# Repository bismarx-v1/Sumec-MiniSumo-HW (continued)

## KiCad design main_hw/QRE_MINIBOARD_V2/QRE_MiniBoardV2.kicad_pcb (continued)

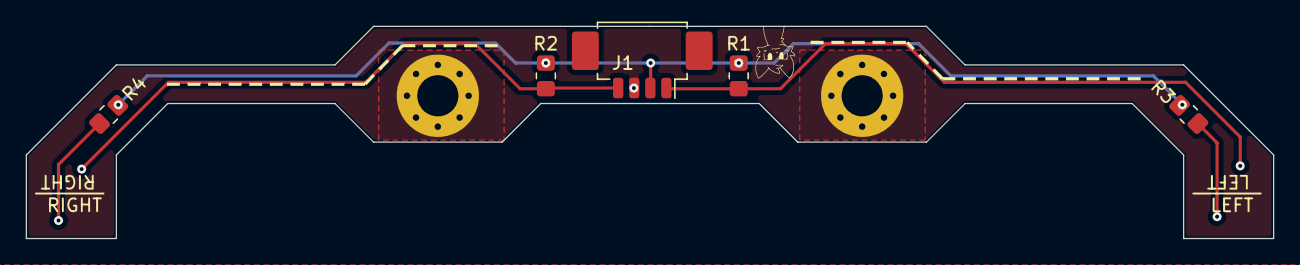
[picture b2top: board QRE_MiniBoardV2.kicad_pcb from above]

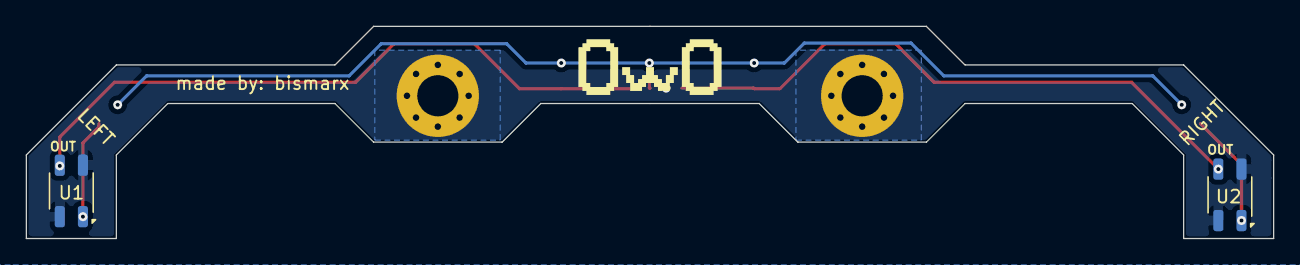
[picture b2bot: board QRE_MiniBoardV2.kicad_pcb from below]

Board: 2 copper layers, 97.0 x 16.5 mm, 11 parts (3 on the bottom side), 6 nets.

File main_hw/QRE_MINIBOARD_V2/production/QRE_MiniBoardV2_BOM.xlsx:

Designator | Footprint | Quantity | Value | Link
J1 | Molex_PicoBlade_53261-0471_1x04-1MP_P1.25mm_Horizontal | 1 | Conn_01x04_Pin | Molex PicoBlade, 4 Pin, horizontal, mouser
R1, R2 | 0805 | 2 | 10k
R3, R4 | 0805 | 2 | 100R
U1, U2 | OnSemi_CASE100CY | 2 | QRE1113 | QRE1113GR

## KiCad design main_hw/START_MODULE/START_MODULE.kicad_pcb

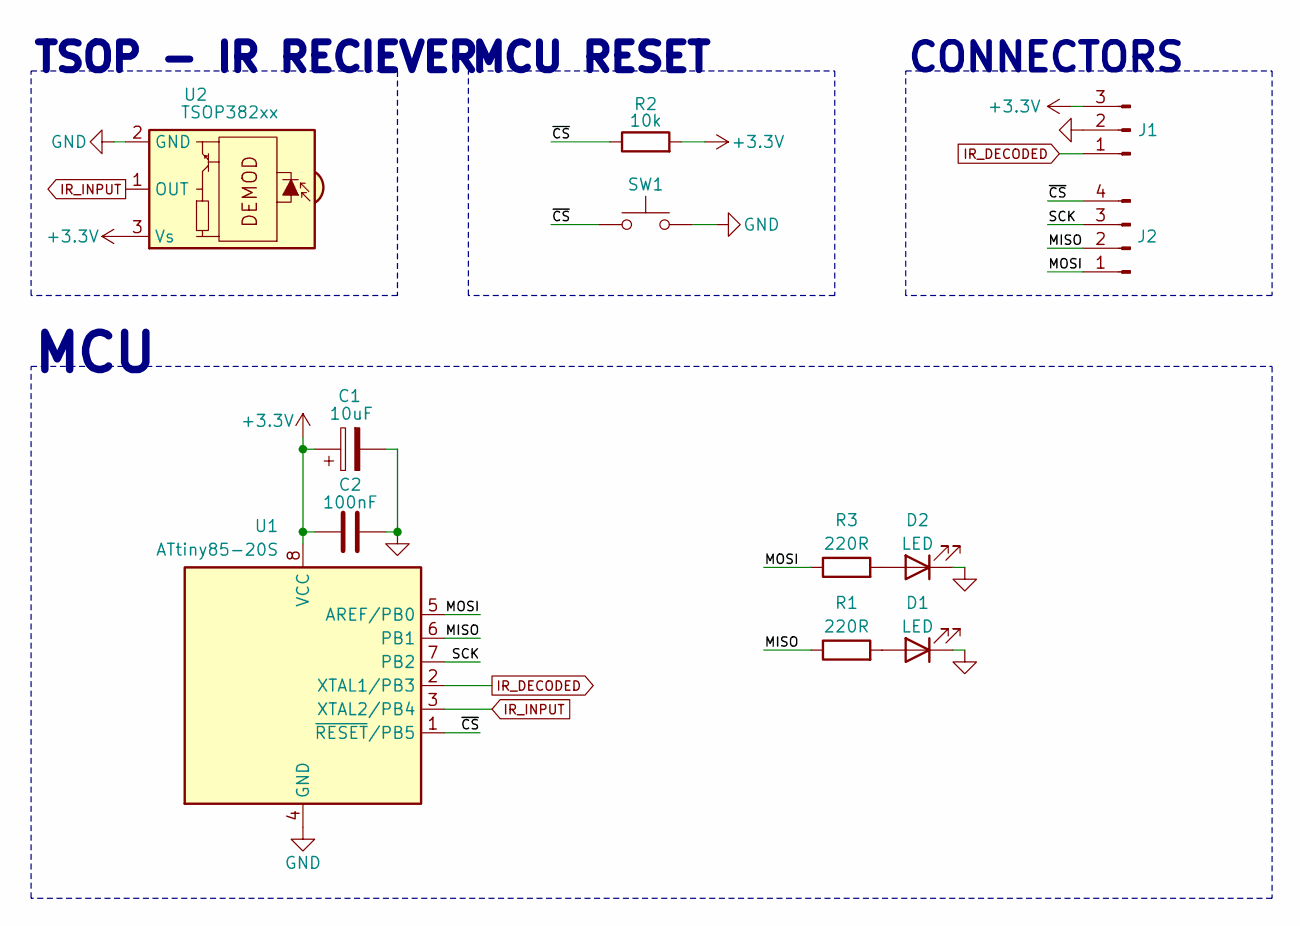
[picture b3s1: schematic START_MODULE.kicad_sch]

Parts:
C1: 10uF; CP_EIA-3216-18_Kemet-A_Pad1.58x1.35mm_HandSolder
C2: 100nF; C_0805_2012Metric_Pad1.18x1.45mm_HandSolder
D1, D2: LED; LED_0805_2012Metric_Pad1.15x1.40mm_HandSolder
J1: Conn_01x03_Pin; PinHeader_1x03_P2.54mm_Horizontal
J2: Conn_01x04_Pin; PinHeader_1x04_P2.54mm_Vertical
R1, R3: 220R; R_0805_2012Metric_Pad1.20x1.40mm_HandSolder
R2: 10k; R_0805_2012Metric_Pad1.20x1.40mm_HandSolder
SW1: SW_Push; SW_SPST_EVQPE1
U1: ATtiny85-20S; SOIC-8W_5.3x5.3mm_P1.27mm
U2: TSOP382xx; Vishay_MINICAST-3Pin

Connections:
+3.3V: C1.1, C2.1, J1.3, R2.2, U1.8 (VCC), U2.3 (Vs)
/MISO: J2.2, R1.1, U1.6 (PB1)
/MOSI: J2.1, R3.1, U1.5 (AREF/PB0)
/SCK: J2.3, U1.7 (PB2)
/~CS: J2.4, R2.1, SW1.2, U1.1 (~RESET/PB5)
GND: C1.2, C2.2, D1.1 (K), D2.1 (K), J1.2, SW1.1, U1.4 (GND), U2.2 (GND)
IR_DECODED: J1.1, U1.2 (XTAL1/PB3)
IR_INPUT: U1.3 (XTAL2/PB4), U2.1 (OUT)
unnamed: D1.2 (A), R1.2
unnamed: D2.2 (A), R3.2

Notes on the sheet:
MCU
TSOP - IR RECIEVER
CONNECTORS
MCU RESET

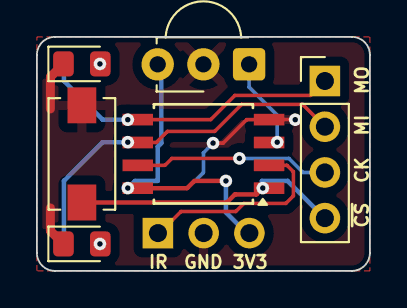
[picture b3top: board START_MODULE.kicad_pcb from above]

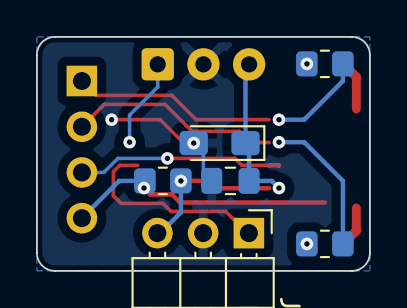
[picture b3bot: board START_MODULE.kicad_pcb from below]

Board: 2 copper layers, 18.5 x 13.0 mm, 12 parts (6 on the bottom side), 10 nets.

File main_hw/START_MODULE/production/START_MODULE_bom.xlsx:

Designator | Footprint | Quantity | Value | Link
C1 | CP_EIA-3216-18_Kemet-A_Pad1.58x1.35mm_HandSolder | 1 | 10uF
C2 | 0805 | 1 | 100nF
D1, D2 | 0805 | 2 | LED
R1, R3 | 0805 | 2 | 220R
R2 | 0805 | 1 | 10k
J1 | PinHeader_1x03_P2.54mm_Vertical | 1 | Conn_01x03_Pin
J2 | PinHeader_1x04_P2.54mm_Vertical | 1 | Conn_01x04_Pin
SW1 | SW_SPST_EVQPE1 | 1 | SW_Push
U1 | SOIC-8W_5.3x5.3mm_P1.27mm | 1 | ATtiny85-20S | ATtiny85-20S
U2 | Vishay_MINICAST-3Pin | 1 | TSOP382xx

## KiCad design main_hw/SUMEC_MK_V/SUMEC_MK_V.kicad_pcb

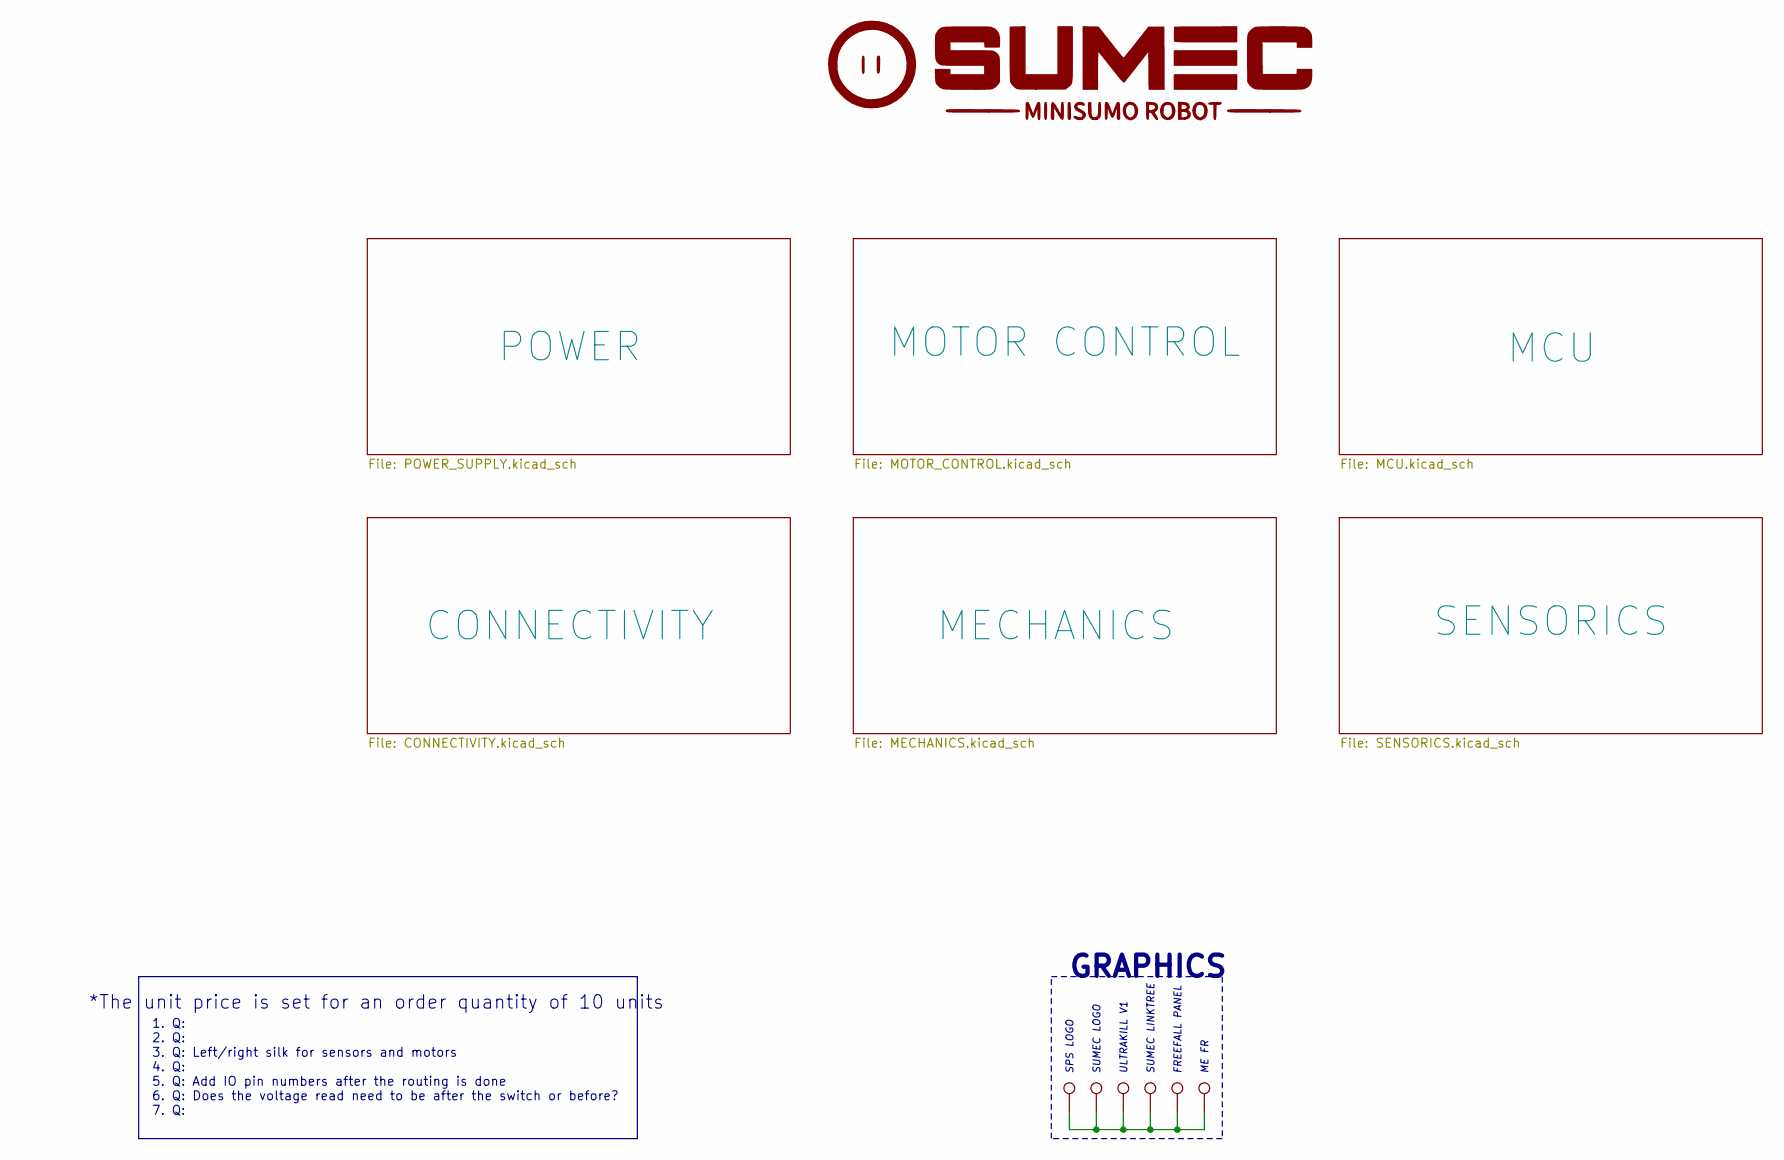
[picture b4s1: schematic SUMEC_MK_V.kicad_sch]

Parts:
TP1, TP2, TP3, TP4, TP5, TP6: TestPoint

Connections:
unnamed: TP1.1, TP2.1, TP3.1, TP4.1, TP5.1, TP6.1

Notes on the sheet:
SUMEC LINKTREE
GRAPHICS
ULTRAKILL V1
1. Q: 2. Q: 3. Q: Left/right silk for sensors and motors 4. Q: 5. Q: Add IO pin numbers after the routing is done 6. Q: Does the voltage read need to be after the switch or before? 7. Q:
SPS LOGO
*The unit price is set for an order quantity of 10 units
SUMEC LOGO
ME FR
FREEFALL PANEL

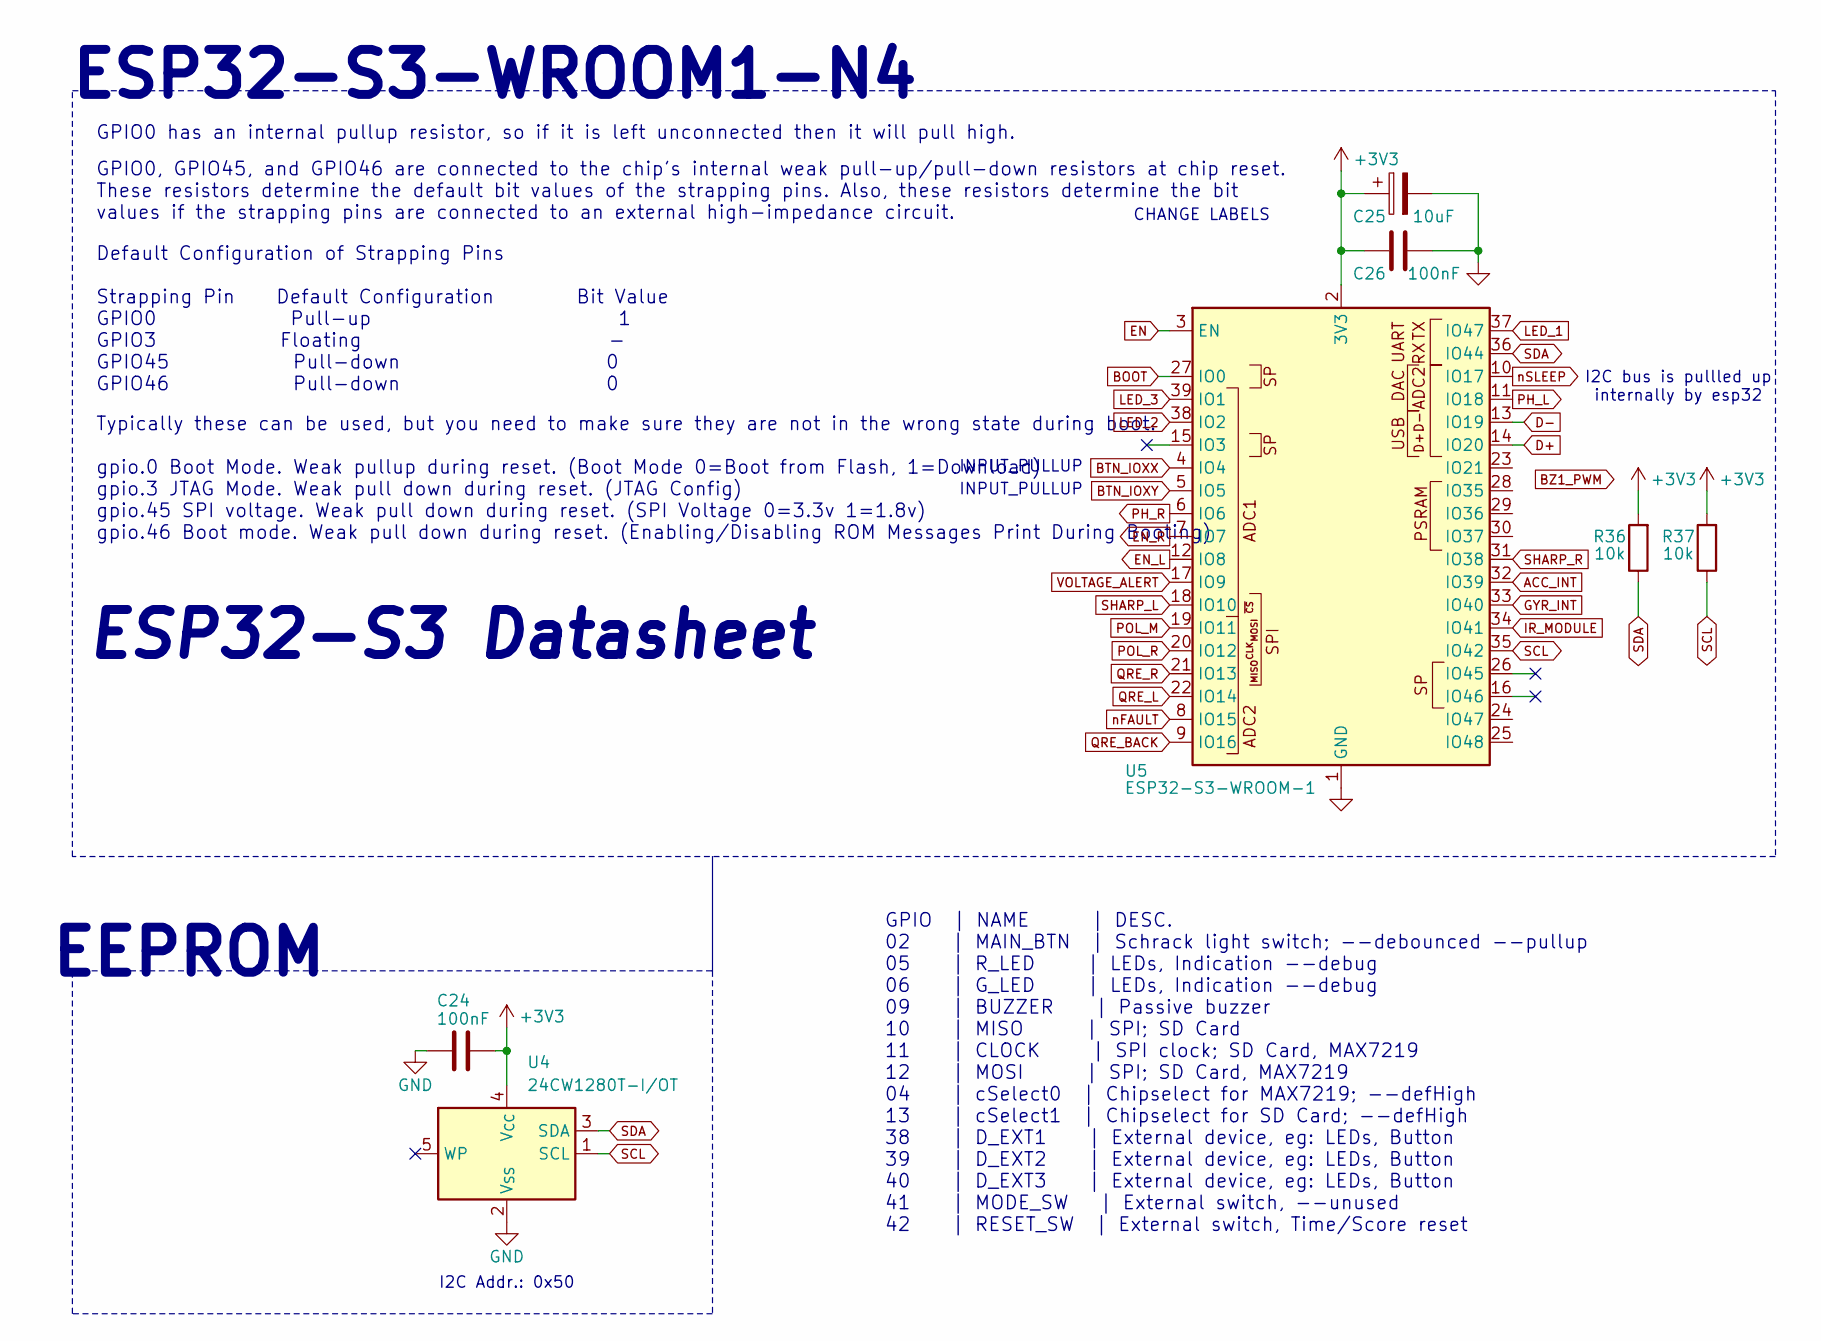
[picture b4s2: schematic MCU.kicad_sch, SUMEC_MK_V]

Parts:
C24, C26: 100nF; C_0805_2012Metric_Pad1.18x1.45mm_HandSolder
C25: 10uF; CP_EIA-3216-18_Kemet-A_Pad1.58x1.35mm_HandSolder
R36, R37: 10k; R_0805_2012Metric_Pad1.20x1.40mm_HandSolder
U4: 24CW1280T-I/OT; SOT-23-5
U5: ESP32-S3-WROOM-1

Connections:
+3V3: C24.1, C25.1, C26.1, R36.2, R37.2, U4.4 (V_{CC}), U5.2 (3V3); also elsewhere on the board
ACC_INT: U5.32 (IO39); also elsewhere on the board
BOOT: U5.27 (IO0); also elsewhere on the board
BTN_IOXX: U5.4 (IO4); also elsewhere on the board
BTN_IOXY: U5.5 (IO5); also elsewhere on the board
D+: U5.14 (IO20); also elsewhere on the board
D-: U5.13 (IO19); also elsewhere on the board
EN: U5.3 (EN); also elsewhere on the board
EN_L: U5.12 (IO8); also elsewhere on the board
EN_R: U5.7 (IO7); also elsewhere on the board
GND: C24.2, C25.2, C26.2, U4.2 (V_{SS}), U5.1 (GND), U5.40 (GND), U5.41 (GND); also elsewhere on the board
GYR_INT: U5.33 (IO40); also elsewhere on the board
IR_MODULE: U5.34 (IO41); also elsewhere on the board
LED_1: U5.37 (IO47); also elsewhere on the board
LED_2: U5.38 (IO2); also elsewhere on the board
LED_3: U5.39 (IO1); also elsewhere on the board
PH_L: U5.11 (IO18); also elsewhere on the board
PH_R: U5.6 (IO6); also elsewhere on the board
POL_M: U5.19 (IO11); also elsewhere on the board
POL_R: U5.20 (IO12); also elsewhere on the board
QRE_BACK: U5.9 (IO16); also elsewhere on the board
QRE_L: U5.22 (IO14); also elsewhere on the board
QRE_R: U5.21 (IO13); also elsewhere on the board
SCL: R37.1, U4.1 (SCL), U5.35 (IO42); also elsewhere on the board
SDA: R36.1, U4.3 (SDA), U5.36 (IO44); also elsewhere on the board
SHARP_L: U5.18 (IO10); also elsewhere on the board
SHARP_R: U5.31 (IO38); also elsewhere on the board
VOLTAGE_ALERT: U5.17 (IO9); also elsewhere on the board
nFAULT: U5.8 (IO15); also elsewhere on the board
nSLEEP: U5.10 (IO17); also elsewhere on the board

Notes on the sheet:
Typically these can be used, but you need to make sure they are not in the wrong state during boot. gpio.0 Boot Mode. Weak pullup during reset. (Boot Mode 0=Boot from Flash, 1=Download) gpio.3 JTAG Mode. Weak pull down during reset. (JTAG Config) gpio.45 SPI voltage. Weak pull down during reset. (S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
GPIO0 has an internal pullup resistor, so if it is left unconnected then it will pull high.
GPIO | NAME | DESC. 02 | MAIN_BTN | Schrack light switch; --debounced --pullup 05 | R_LED | LEDs, Indication --debug 06 | G_LED | LEDs, Indication --debug 09 | BUZZER | Passive buzzer 10 | MISO | SPI; SD Card 11 | CLOCK | SPI clock; SD Card, MAX7219 12 | MOSI | SPI; SD Card, MAX7219 04 | cSelect0 |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
ESP32-S3-WROOM1-N4
I2C Addr.: 0x50
GPIO0, GPIO45, and GPIO46 are connected to the chip's internal weak pull-up/pull-down resistors at chip reset. These resistors determine the default bit values of the strapping pins. Also, these resistors determine the bit values if the strapping pins are connected to an external high-impedance cir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
CHANGE LABELS
I2C bus is pullled up internally by esp32
ESP32-S3 Datasheet
INPUT_PULLUP
EEPROM
Default Configuration of Strapping Pins Strapping Pin Default Configuration Bit Value GPIO0 Pull-up 1 GPIO3 Floating - GPIO45 Pull-down 0 GPIO46 Pull-down 0

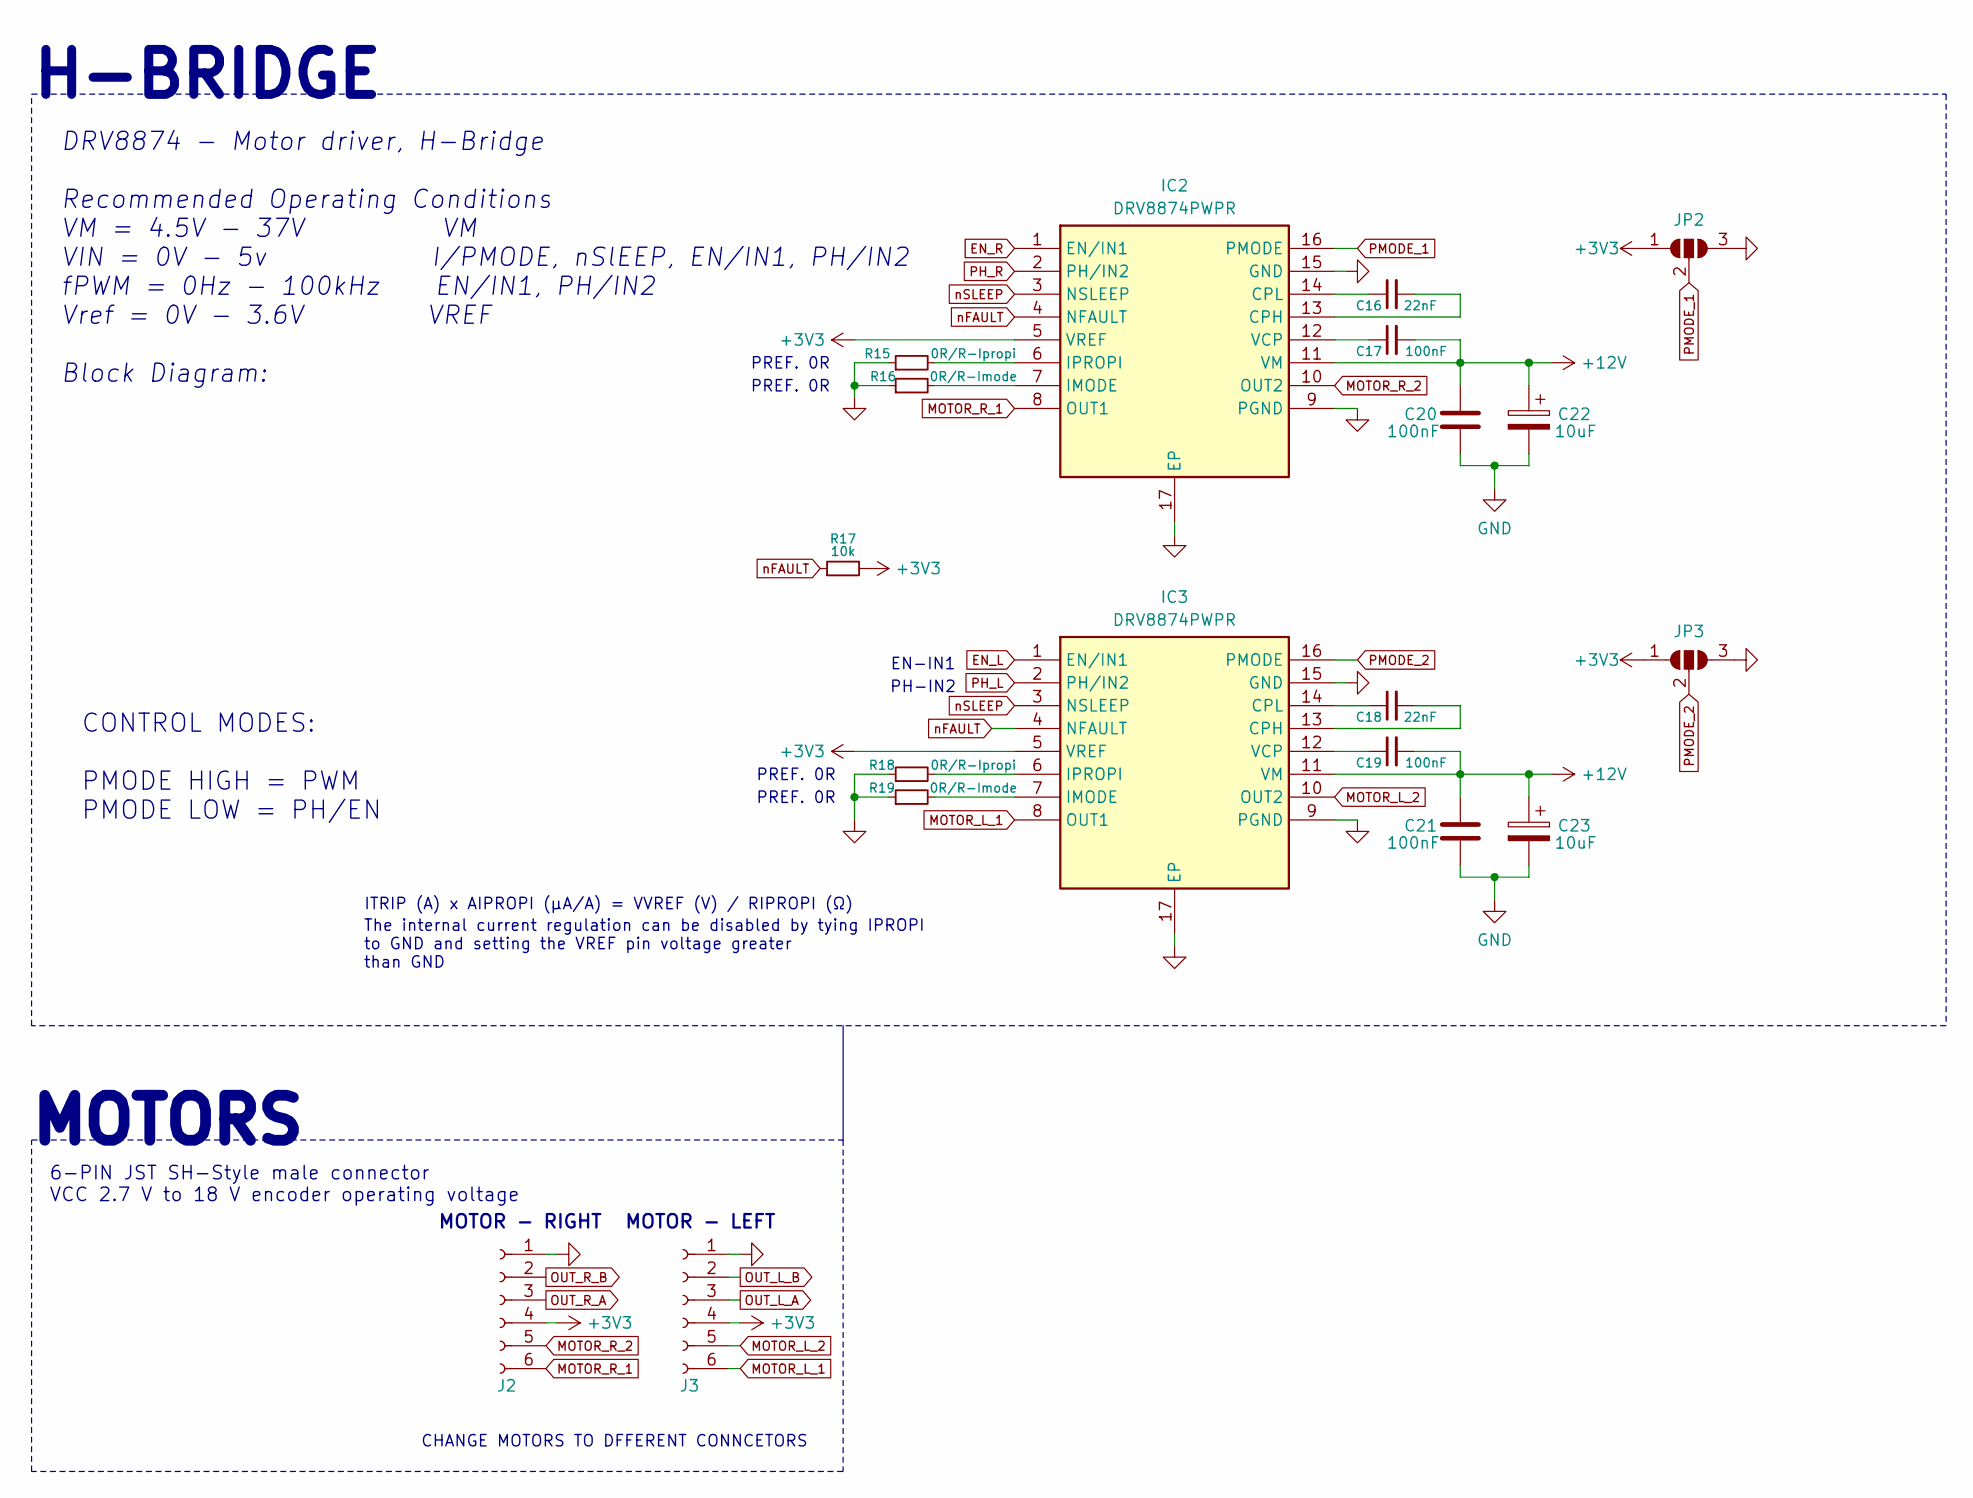
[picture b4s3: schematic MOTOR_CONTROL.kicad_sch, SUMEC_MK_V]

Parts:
C16, C18: 22nF; C_0805_2012Metric_Pad1.18x1.45mm_HandSolder
C17, C19, C20, C21: 100nF; C_0805_2012Metric_Pad1.18x1.45mm_HandSolder
C22, C23: 10uF; CP_EIA-3216-18_Kemet-A_Pad1.58x1.35mm_HandSolder
IC2, IC3: DRV8874PWPR; DRV8874; Manufacturer_Part_Number DRV8874PWPR; Mouser Part Number 595-DRV8874PWPR
J2, J3: Conn_01x06_Socket; JST_SH_BM06B-SRSS-TB_1x06-1MP_P1.00mm_Vertical
JP2, JP3: SolderJumper_3_Open; SolderJumper-3_P2.0mm_Open_TrianglePad1.0x1.5mm
R15, R18: 0R/R-Ipropi; R_0805_2012Metric_Pad1.20x1.40mm_HandSolder
R16, R19: 0R/R-Imode; R_0805_2012Metric_Pad1.20x1.40mm_HandSolder
R17: 10k; R_0805_2012Metric_Pad1.20x1.40mm_HandSolder

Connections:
+3V3: IC2.5 (VREF), IC3.5 (VREF), J2.4, J3.4, JP2.1 (A), JP3.1 (A), R17.2; also elsewhere on the board
+12V: C17.2, C19.2, C20.2, C21.2, C22.1, C23.1, IC2.11 (VM), IC3.11 (VM); also elsewhere on the board
EN_L: IC3.1 (EN/IN1); also elsewhere on the board
EN_R: IC2.1 (EN/IN1); also elsewhere on the board
GND: C20.1, C21.1, C22.2, C23.2, IC2.9 (PGND), IC2.15 (GND), IC2.17 (EP), IC3.9 (PGND), IC3.15 (GND), IC3.17 (EP), J2.1, J3.1, JP2.3 (B), JP3.3 (B), R15.1, R16.1, R18.1, R19.1; also elsewhere on the board
MOTOR_L_1: IC3.8 (OUT1), J3.6
MOTOR_L_2: IC3.10 (OUT2), J3.5
MOTOR_R_1: IC2.8 (OUT1), J2.6
MOTOR_R_2: IC2.10 (OUT2), J2.5
unnamed: C16.2, IC2.13 (CPH)
unnamed: C16.1, IC2.14 (CPL)
unnamed: IC2.7 (IMODE), R16.2
unnamed: IC2.6 (IPROPI), R15.2
unnamed: C17.1, IC2.12 (VCP)
unnamed: C18.2, IC3.13 (CPH)
unnamed: C18.1, IC3.14 (CPL)
unnamed: IC3.7 (IMODE), R19.2
unnamed: IC3.6 (IPROPI), R18.2
unnamed: C19.1, IC3.12 (VCP)
OUT_L_A: J3.3
OUT_L_B: J3.2
OUT_R_A: J2.3
OUT_R_B: J2.2
PH_L: IC3.2 (PH/IN2); also elsewhere on the board
PH_R: IC2.2 (PH/IN2); also elsewhere on the board
PMODE_1: IC2.16 (PMODE), JP2.2 (C)
PMODE_2: IC3.16 (PMODE), JP3.2 (C)
nFAULT: IC2.4 (NFAULT), IC3.4 (NFAULT), R17.1; also elsewhere on the board
nSLEEP: IC2.3 (NSLEEP), IC3.3 (NSLEEP); also elsewhere on the board

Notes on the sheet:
CHANGE MOTORS TO DFFERENT CONNCETORS
PREF. 0R
CONTROL MODES: PMODE HIGH = PWM PMODE LOW = PH/EN
The internal current regulation can be disabled by tying IPROPI to GND and setting the VREF pin voltage greater than GND
EN-IN1
DRV8874 - Motor driver, H-Bridge Recommended Operating Conditions VM = 4.5V - 37V VM VIN = 0V - 5v I/PMODE, nSlEEP, EN/IN1, PH/IN2 fPWM = 0Hz - 100kHz EN/IN1, PH/IN2 Vref = 0V - 3.6V VREF Block Diagram:
ITRIP (A) x AIPROPI (μA/A) = VVREF (V) / RIPROPI (Ω)
H-BRIDGE
6-PIN JST SH-Style male connector VCC 2.7 V to 18 V encoder operating voltage
MOTORS
MOTOR - LEFT
MOTOR - RIGHT
PH-IN2

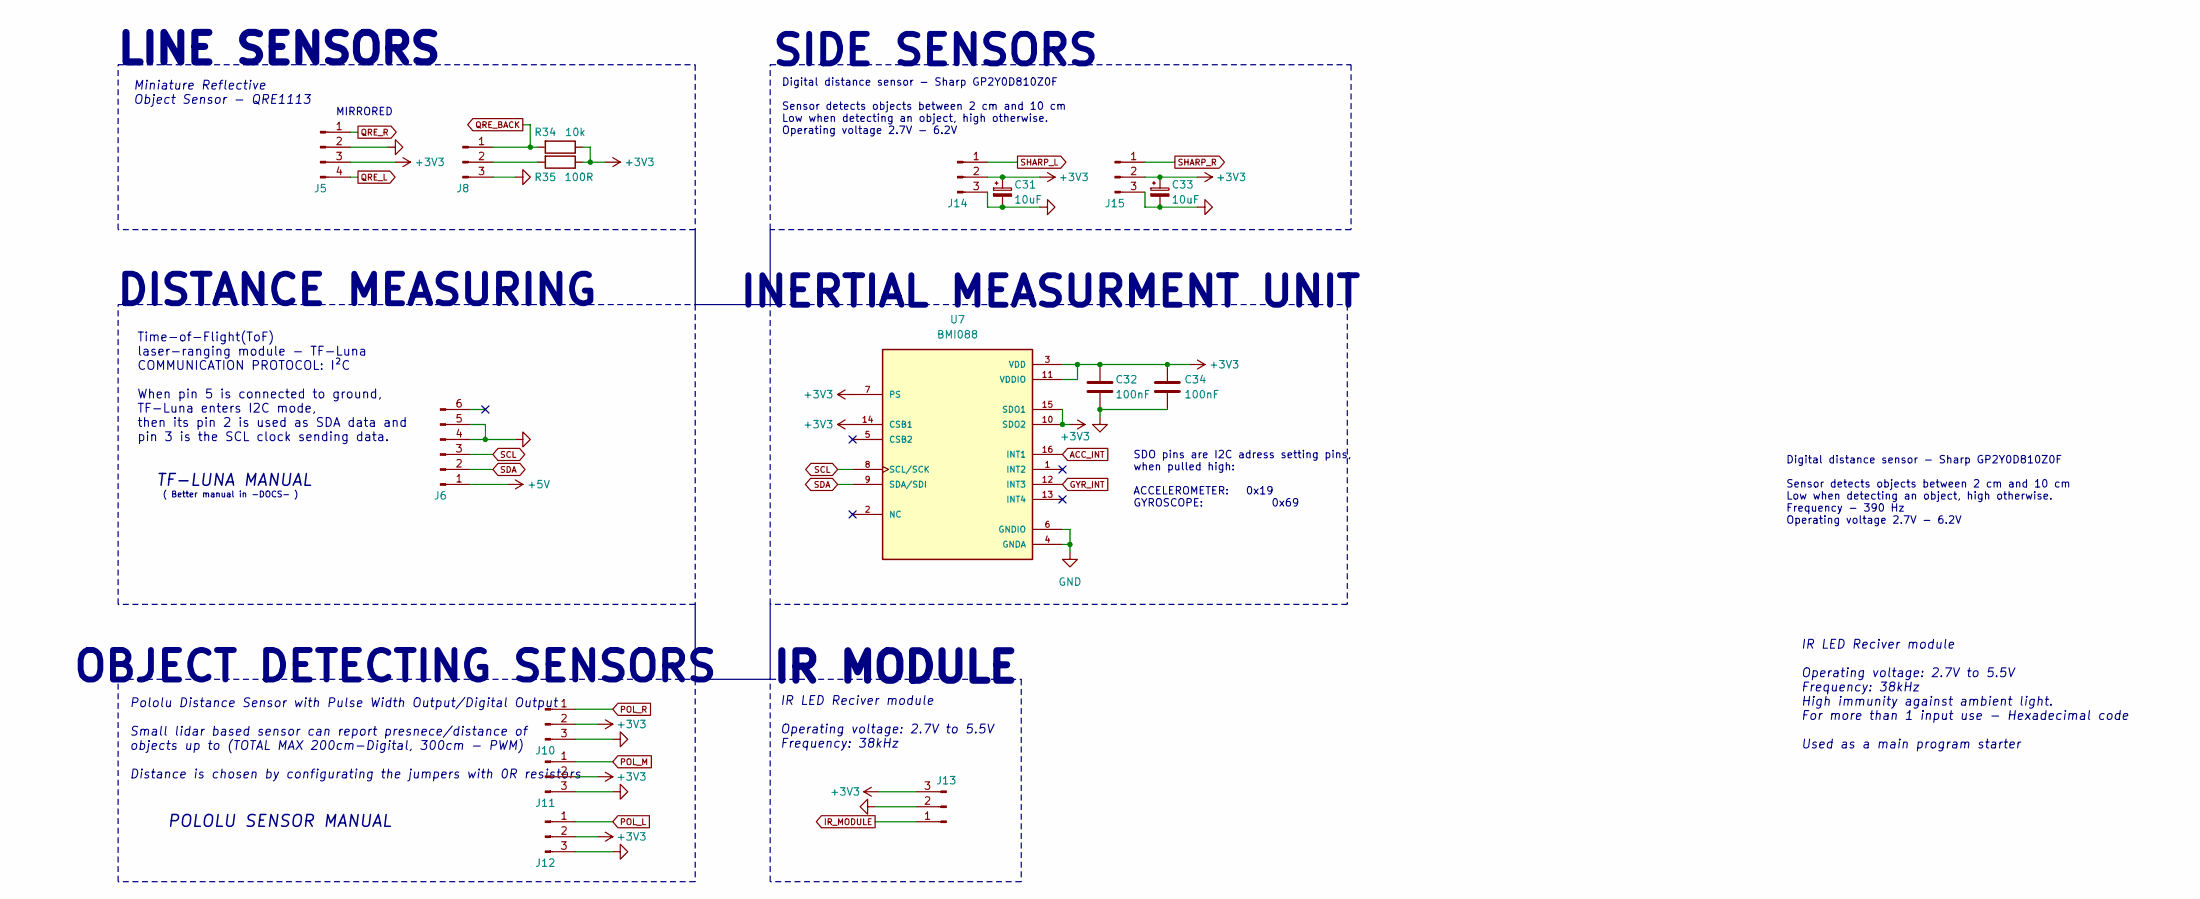
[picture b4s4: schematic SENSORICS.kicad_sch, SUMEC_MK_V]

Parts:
C31, C33: 10uF; CP_EIA-3216-18_Kemet-A_Pad1.58x1.35mm_HandSolder
C32, C34: 100nF; C_0805_2012Metric_Pad1.18x1.45mm_HandSolder
J5: Conn_01x04_Pin; Molex_PicoBlade_53398-0471_1x04-1MP_P1.25mm_Vertical
J6: Conn_01x06_Pin; Molex_PicoBlade_53398-0671_1x06-1MP_P1.25mm_Vertical
J8, J10, J11, J12, J14, J15: Conn_01x03_Pin; Molex_PicoBlade_53398-0371_1x03-1MP_P1.25mm_Vertical
J13: Conn_01x03_Pin; PinHeader_1x03_P2.54mm_Vertical
R34: 10k; R_0805_2012Metric_Pad1.20x1.40mm_HandSolder
R35: 100R; R_0805_2012Metric_Pad1.20x1.40mm_HandSolder
U7: BMI088; PQFN50P450X300X100-16N

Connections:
+3V3: C31.1, C32.2, C33.1, C34.2, J5.3, J10.2, J11.2, J12.2, J13.3, J14.2, J15.2, R34.1, R35.1, U7.3 (VDD), U7.7 (PS), U7.10 (SDO2), U7.11 (VDDIO), U7.14 (CSB1), U7.15 (SDO1); also elsewhere on the board
+5V: J6.1; also elsewhere on the board
ACC_INT: U7.16 (INT1); also elsewhere on the board
GND: C31.2, C32.1, C33.2, C34.1, J5.2, J6.4, J6.5, J8.3, J10.3, J11.3, J12.3, J13.2, J14.3, J15.3, U7.4 (GNDA), U7.6 (GNDIO); also elsewhere on the board
GYR_INT: U7.12 (INT3); also elsewhere on the board
IR_MODULE: J13.1; also elsewhere on the board
unnamed: J8.2, R35.2
POL_L: J12.1
POL_M: J11.1; also elsewhere on the board
POL_R: J10.1; also elsewhere on the board
QRE_BACK: J8.1, R34.2; also elsewhere on the board
QRE_L: J5.4; also elsewhere on the board
QRE_R: J5.1; also elsewhere on the board
SCL: J6.3, U7.8 (SCL/SCK); also elsewhere on the board
SDA: J6.2, U7.9 (SDA/SDI); also elsewhere on the board
SHARP_L: J14.1; also elsewhere on the board
SHARP_R: J15.1; also elsewhere on the board

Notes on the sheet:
IR MODULE
( Better manual in -DOCS- )
IR LED Reciver module Operating voltage: 2.7V to 5.5V Frequency: 38kHz
Time-of-Flight(ToF) laser-ranging module - TF-Luna COMMUNICATION PROTOCOL: I²C When pin 5 is connected to ground, TF-Luna enters I2C mode, then its pin 2 is used as SDA data and pin 3 is the SCL clock sending data.
Digital distance sensor - Sharp GP2Y0D810Z0F Sensor detects objects between 2 cm and 10 cm Low when detecting an object, high otherwise. Operating voltage 2.7V - 6.2V
SIDE SENSORS
Pololu Distance Sensor with Pulse Width Output/Digital Output Small lidar based sensor can report presnece/distance of objects up to (TOTAL MAX 200cm-Digital, 300cm - PWM) Distance is chosen by configurating the jumpers with 0R resistors
POLOLU SENSOR MANUAL
TF-LUNA MANUAL
Digital distance sensor - Sharp GP2Y0D810Z0F Sensor detects objects between 2 cm and 10 cm Low when detecting an object, high otherwise. Frequency - 390 Hz Operating voltage 2.7V - 6.2V
IR LED Reciver module Operating voltage: 2.7V to 5.5V Frequency: 38kHz High immunity against ambient light. For more than 1 input use - Hexadecimal code Used as a main program starter
OBJECT DETECTING SENSORS
MIRRORED
DISTANCE MEASURING
SDO pins are I2C adress setting pins, when pulled high: ACCELEROMETER: 0x19 GYROSCOPE: 0x69
INERTIAL MEASURMENT UNIT
LINE SENSORS
Miniature Reflective Object Sensor - QRE1113

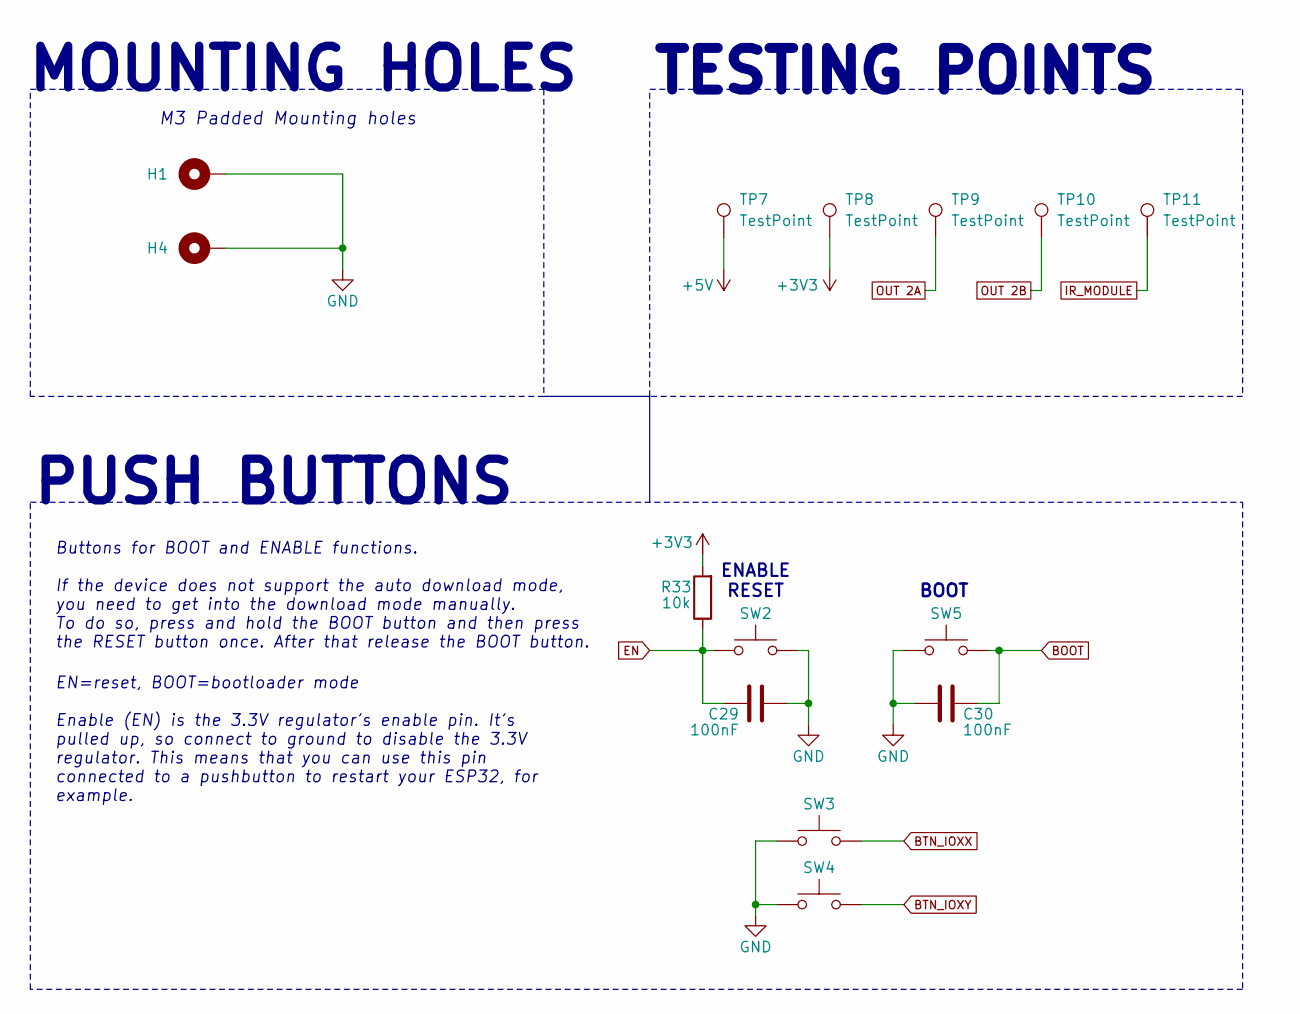
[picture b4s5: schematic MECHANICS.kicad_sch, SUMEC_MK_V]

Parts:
C29, C30: 100nF; C_0805_2012Metric_Pad1.18x1.45mm_HandSolder
H1, H4: Mounting Hole M3; MountingHole_3.2mm_M3_Pad_Via
R33: 10k; R_0805_2012Metric_Pad1.20x1.40mm_HandSolder
SW2, SW3, SW4, SW5: SW_Push; SW_SPST_EVQPE1
TP7, TP8, TP9, TP10, TP11: TestPoint; TestPoint_Pad_1.0x1.0mm

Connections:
+3V3: R33.2, TP8.1; also elsewhere on the board
+5V: TP7.1; also elsewhere on the board
BOOT: C30.1, SW5.2; also elsewhere on the board
BTN_IOXX: SW3.2; also elsewhere on the board
BTN_IOXY: SW4.2; also elsewhere on the board
EN: C29.1, R33.1, SW2.2; also elsewhere on the board
GND: C29.2, C30.2, H1.1, H4.1, SW2.1, SW3.1, SW4.1, SW5.1; also elsewhere on the board
IR_MODULE: TP11.1; also elsewhere on the board
OUT 2A: TP9.1
OUT 2B: TP10.1

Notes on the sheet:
Buttons for BOOT and ENABLE functions. If the device does not support the auto download mode, you need to get into the download mode manually. To do so, press and hold the BOOT button and then press the RESET button once. After that release the BOOT button.
M3 Padded Mounting holes
ENABLE RESET
EN=reset, BOOT=bootloader mode Enable (EN) is the 3.3V regulator's enable pin. It's pulled up, so connect to ground to disable the 3.3V regulator. This means that you can use this pin connected to a pushbutton to restart your ESP32, for example.
BOOT
TESTING POINTS
PUSH BUTTONS
MOUNTING HOLES

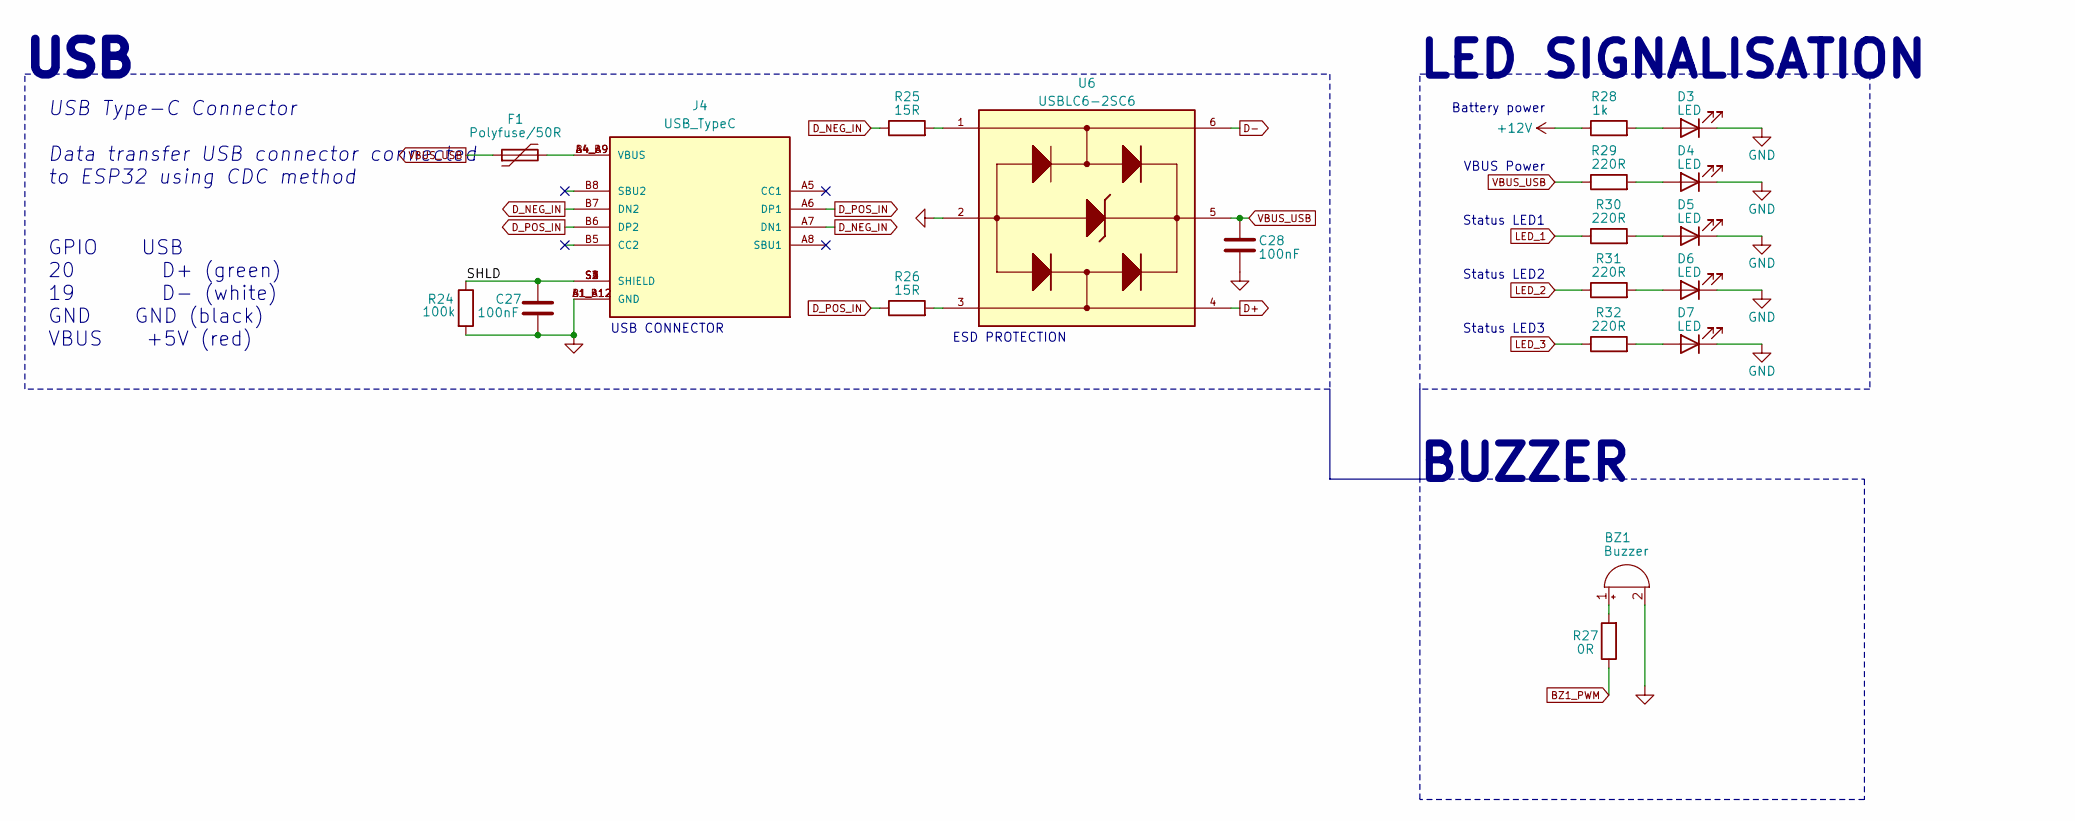
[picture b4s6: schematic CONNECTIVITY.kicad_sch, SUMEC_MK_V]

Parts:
BZ1: Buzzer; BUZZER_CUI_CPT
C27, C28: 100nF; C_0805_2012Metric_Pad1.18x1.45mm_HandSolder
D3, D4, D5, D6, D7: LED; LED_0805_2012Metric_Pad1.15x1.40mm_HandSolder
F1: Polyfuse/50R; Fuse_0805_2012Metric
J4: USB_TypeC; HRO_TYPE-C-31-M-12; PARTREV 2020.12.08
R24: 100k; R_0805_2012Metric_Pad1.20x1.40mm_HandSolder
R25, R26: 15R; R_0805_2012Metric_Pad1.20x1.40mm_HandSolder
R27: 0R; R_0805_2012Metric_Pad1.20x1.40mm_HandSolder
R28: 1k; R_0805_2012Metric_Pad1.20x1.40mm_HandSolder
R29, R30, R31, R32: 220R; R_0805_2012Metric_Pad1.20x1.40mm_HandSolder
U6: USBLC6-2SC6; TSOT-23-6_HandSoldering

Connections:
+12V: R28.1; also elsewhere on the board
/CONNECTIVITY/SHLD: C27.2, J4.S1 (SHIELD), J4.S2 (SHIELD), J4.S3 (SHIELD), J4.S4 (SHIELD), R24.1
BZ1_PWM: R27.1
D+: U6.4; also elsewhere on the board
D-: U6.6; also elsewhere on the board
D_NEG_IN: J4.A7 (DN1), J4.B7 (DN2), R25.1
D_POS_IN: J4.A6 (DP1), J4.B6 (DP2), R26.1
GND: BZ1.2 (-), C27.1, C28.2, D3.1 (K), D4.1 (K), D5.1 (K), D6.1 (K), D7.1 (K), J4.A1_B12 (GND), J4.B1_A12 (GND), R24.2, U6.2; also elsewhere on the board
LED_1: R30.1; also elsewhere on the board
LED_2: R31.1; also elsewhere on the board
LED_3: R32.1; also elsewhere on the board
unnamed: BZ1.1 (+), R27.2
unnamed: D3.2 (A), R28.2
unnamed: D4.2 (A), R29.2
unnamed: D5.2 (A), R30.2
unnamed: D6.2 (A), R31.2
unnamed: D7.2 (A), R32.2
unnamed: F1.2, J4.A4_B9 (VBUS), J4.B4_A9 (VBUS)
unnamed: R25.2, U6.1
unnamed: R26.2, U6.3
VBUS_USB: C28.1, F1.1, R29.1, U6.5; also elsewhere on the board

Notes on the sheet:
VBUS Power
BUZZER
GPIO USB 20 D+ (green) 19 D- (white) GND GND (black) VBUS +5V (red)
Status LED2
LED SIGNALISATION
Battery power
Status LED1
USB
USB Type-C Connector Data transfer USB connector connected to ESP32 using CDC method
ESD PROTECTION
Status LED3
USB CONNECTOR
